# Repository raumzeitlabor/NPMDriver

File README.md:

A small RS485/DMX/RDM driver board for the NPM2000.

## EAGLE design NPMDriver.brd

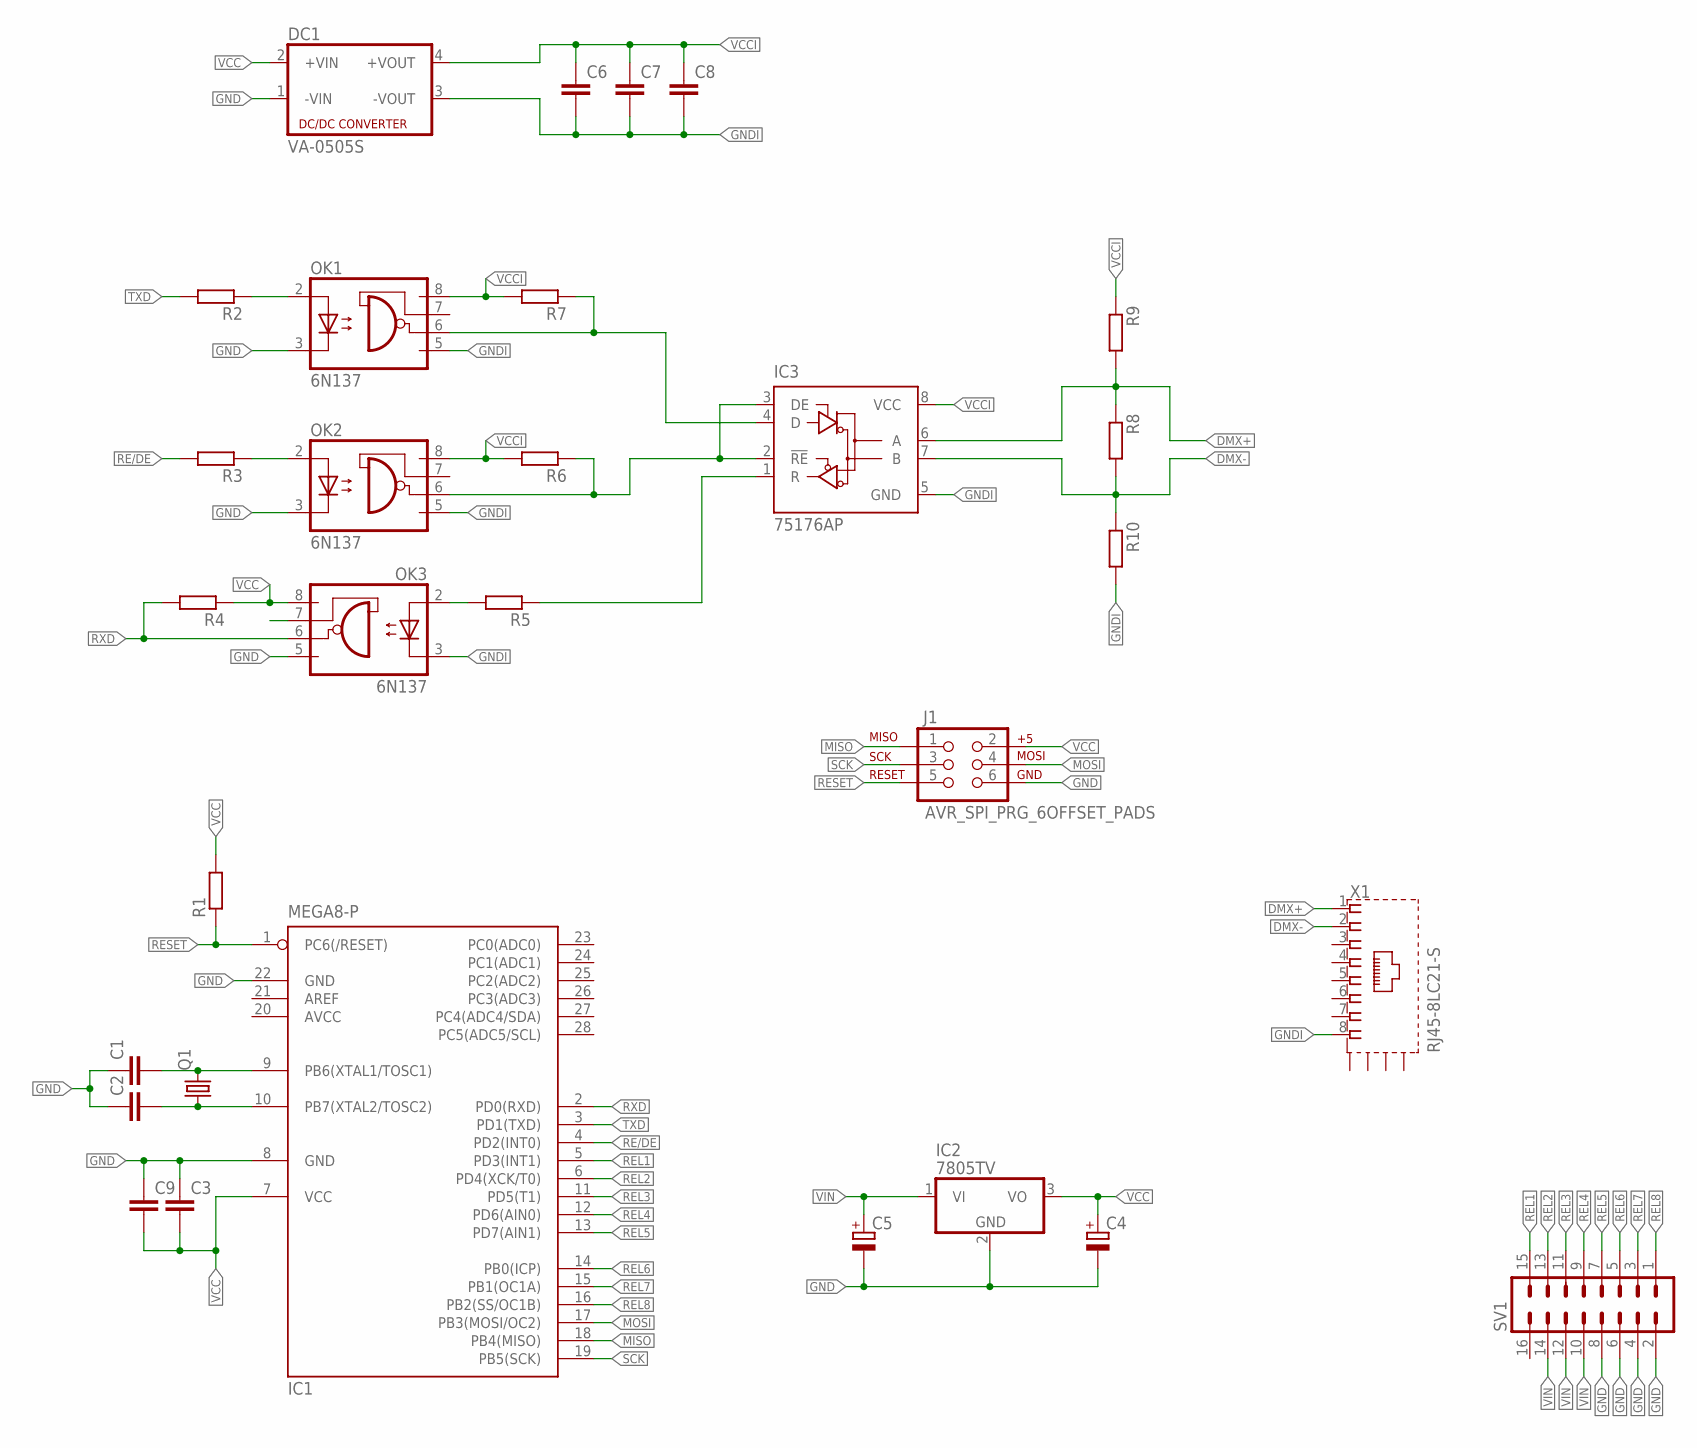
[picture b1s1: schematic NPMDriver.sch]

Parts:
C1, C2: C-EU025-025X050; C025-025X050
C3, C6, C7, C8, C9: C-EU050-035X075; C050-035X075
C4, C5: CPOL-EUE5-8.5; E5-8,5
DC1: VA-0505S; 4SIL
IC1: MEGA8-P; DIL28-3
IC2: 7805TV; TO220V
IC3: 75176AP; DIL08
J1: AVR_SPI_PRG_6OFFSET_PADS; 2X3_OFFSET
OK1, OK2, OK3: 6N137; DIL08
Q1: CRYSTALHC49S; HC49/S
R1, R2, R3, R4, R5, R6, R7, R8, R9, R10: R-EU_0207/10; 0207/10
SV1: ML163M; 3M_16
X1: RJ45-8LC21-S; RJ45-SHIELD1

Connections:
AVCC: IC1.20 (AVCC)
DMX+: IC3.6 (A), R8.1, R9.2, X1.1
DMX-: IC3.7 (B), R8.2, R10.1, X1.2
GND: C1.1, C2.1, C3.1, C4.-, C5.-, C9.1, DC1.1 (-VIN), IC1.8 (GND), IC1.22 (GND), IC2.2 (GND), J1.6, OK1.3 (C), OK2.3 (C), OK3.5 (GND), SV1.2, SV1.4, SV1.6, SV1.8
GNDI: C6.2, C7.2, C8.2, DC1.3 (-VOUT), IC3.5 (GND), OK1.5 (GND), OK2.5 (GND), OK3.3 (C), R10.2, X1.8
MISO: IC1.18 (PB4(MISO)), J1.1
MOSI: IC1.17 (PB3(MOSI/OC2)), J1.4
unnamed: C2.2, IC1.10 (PB7(XTAL2/TOSC2)), Q1.1
unnamed: C1.2, IC1.9 (PB6(XTAL1/TOSC1)), Q1.2
unnamed: OK1.2 (A), R2.1
unnamed: OK3.2 (A), R5.2
unnamed: OK2.2 (A), R3.1
unnamed: IC3.1 (R), R5.1
unnamed: IC3.4 (D), OK1.6 (VO), R7.1
unnamed: IC3.2 (!RE), IC3.3 (DE), OK2.6 (VO), R6.1
RE/DE: IC1.4 (PD2(INT0)), R3.2
REL1: IC1.5 (PD3(INT1)), SV1.15
REL2: IC1.6 (PD4(XCK/T0)), SV1.13
REL3: IC1.11 (PD5(T1)), SV1.11
REL4: IC1.12 (PD6(AIN0)), SV1.9
REL5: IC1.13 (PD7(AIN1)), SV1.7
REL6: IC1.14 (PB0(ICP)), SV1.5
REL7: IC1.15 (PB1(OC1A)), SV1.3
REL8: IC1.16 (PB2(SS/OC1B)), SV1.1
RESET: IC1.1 (PC6(/RESET)), J1.5, R1.1
RXD: IC1.2 (PD0(RXD)), OK3.6 (VO), R4.2
SCK: IC1.19 (PB5(SCK)), J1.3
TXD: IC1.3 (PD1(TXD)), R2.2
VCC: C3.2, C4.+, C9.2, DC1.2 (+VIN), IC1.7 (VCC), IC2.3 (VO), J1.2, OK3.8 (VCC), R1.2, R4.1
VCCI: C6.1, C7.1, C8.1, DC1.4 (+VOUT), IC3.8 (VCC), OK1.8 (VCC), OK2.8 (VCC), R6.2, R7.2, R9.1
VIN: C5.+, IC2.1 (VI), SV1.10, SV1.12, SV1.14

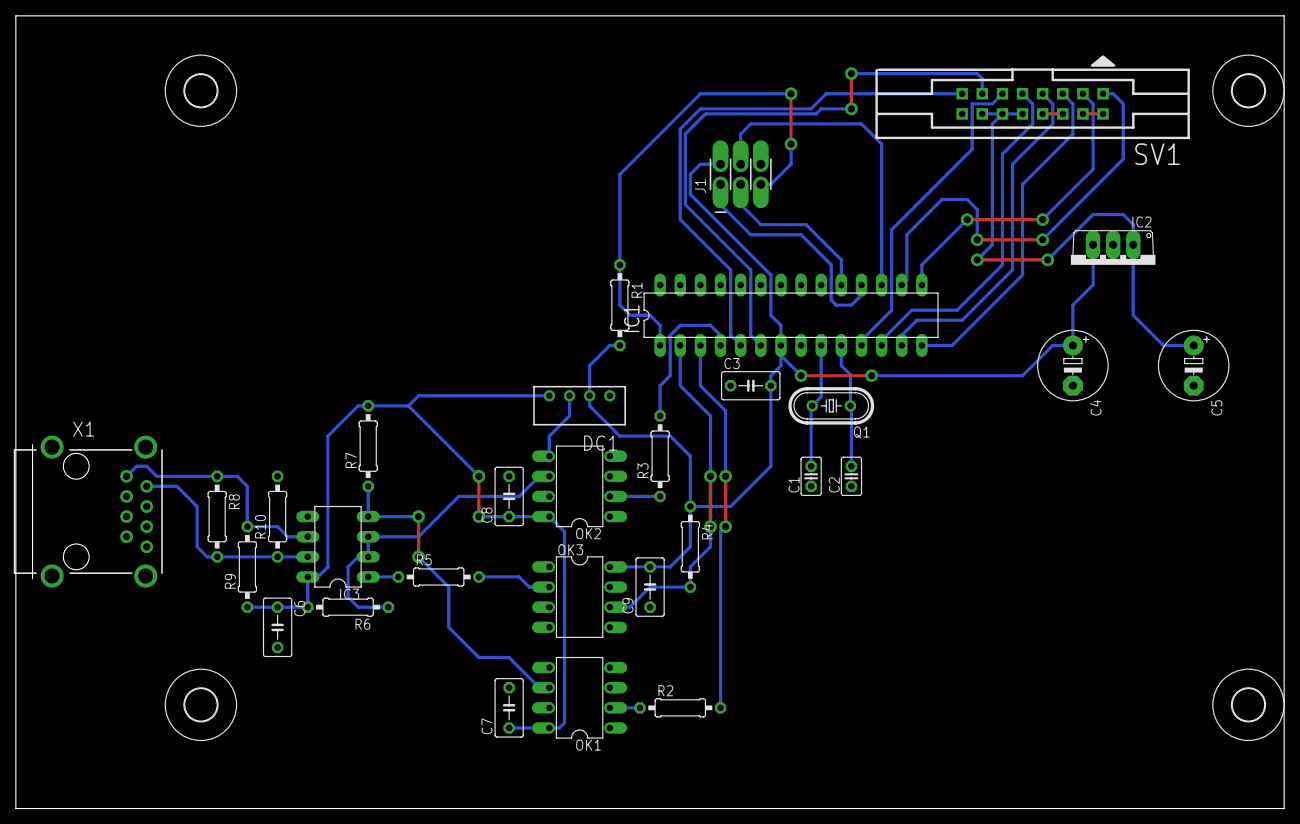
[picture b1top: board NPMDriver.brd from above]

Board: 2 copper layers, 160.0 x 100.0 mm, 34 parts (0 on the bottom side), 30 nets.

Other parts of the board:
U$1, U$2, U$3, U$4: 4,1

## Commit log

2013-11-30 Fixed crystal caps size
2014-02-10 Initial checkin
2014-02-12 Finalized firmware ;)
2014-02-12 Fixed accidentally commented out main functionality, oops!
2014-02-13 Added comment about the firmware and where to find more information

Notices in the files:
parts and their libraries:
SparkFun: Licensing: CC v3.0 Share-Alike You are welcome to use this library for commercial purposes.
